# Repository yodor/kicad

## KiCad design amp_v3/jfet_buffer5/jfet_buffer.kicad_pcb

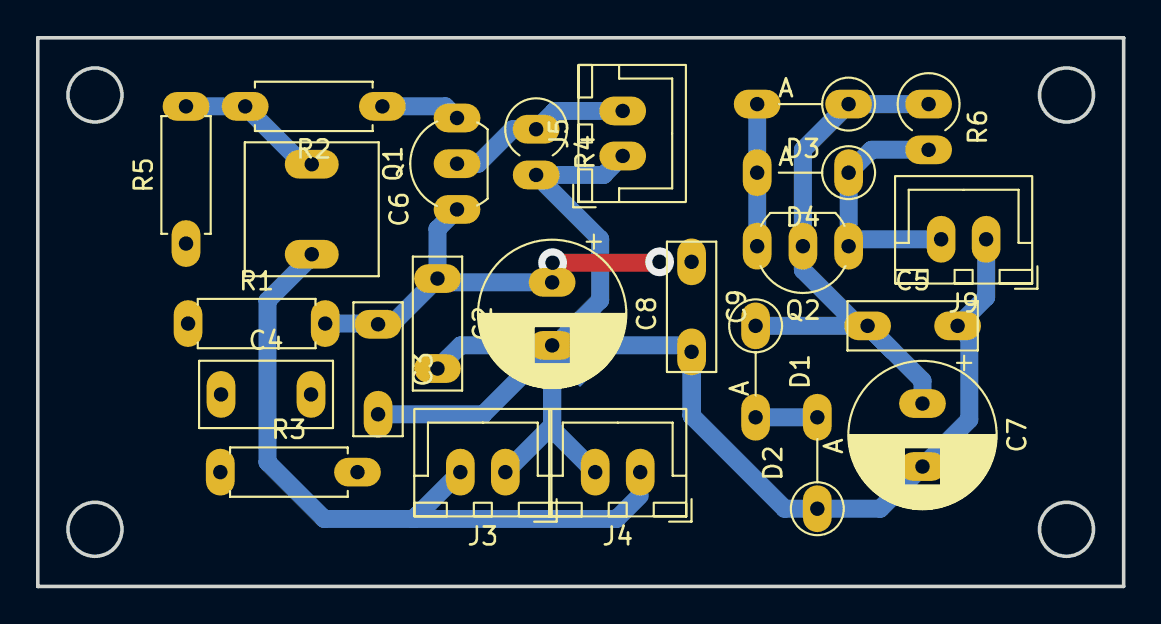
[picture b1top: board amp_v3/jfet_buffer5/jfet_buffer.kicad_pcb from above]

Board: 2 copper layers, 60.3 x 30.5 mm, 25 parts (1 on the bottom side), 10 nets.

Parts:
C2, C3: 100nF; C_Rect_L7.2mm_W2.5mm_P5.00mm_FKS2_FKP2_MKS2_MKP2
C4: 1uF; C_Rect_L7.2mm_W3.5mm_P5.00mm_FKS2_FKP2_MKS2_MKP2
C5, C9: 100nF; C_Rect_L7.0mm_W2.5mm_P5.00mm
C6: 2.2uF; C_Rect_L7.2mm_W7.2mm_P5.00mm_FKS2_FKP2_MKS2_MKP2
C7: 470uF; CP_Radial_D8.0mm_P3.50mm
C8: 470uF (low ESR); CP_Radial_D8.0mm_P3.50mm
D1: 1N4747; D_A-405_P5.08mm_Vertical_AnodeUp
D2: 1n4148; D_A-405_P5.08mm_Vertical_AnodeUp
D3, D4: 1N4007; D_A-405_P5.08mm_Vertical_AnodeUp
J3, J4: AUDIO_IN; JST_XH_B2B-XH-A_1x02_P2.50mm_Vertical
J5: AUDIO_OUT; JST_XH_B2B-XH-A_1x02_P2.50mm_Vertical
J9: PWR_IN; JST_XH_B2B-XH-A_1x02_P2.50mm_Vertical
NT1: NetTie_2; NetTie-2_SMD_Pad1.0o
Q1: 2N5457; TO-92L_Inline_Wide
Q2: BC549C; TO-92_Inline_Wide
R1, R3, R5: 1M; R_Axial_DIN0207_L6.3mm_D2.5mm_P7.62mm_Horizontal
R2: 100; R_Axial_DIN0207_L6.3mm_D2.5mm_P7.62mm_Horizontal
R4: 3.9K; R_Axial_DIN0309_L9.0mm_D3.2mm_P2.54mm_Vertical
R6: 240; R_Axial_DIN0309_L9.0mm_D3.2mm_P2.54mm_Vertical

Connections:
/20V_JFET: C2.1, C3.1, C8.1, C9.1, D3.2 (A), D4.2 (A), Q1.1 (D), Q2.3 (E), R1.2
/22V_REG: D4.1 (K), J9.2, Q2.1 (C), R6.2
/INPUT: C6.2, J3.2, J4.1
/OUT: J5.2, Q1.2 (S), R4.1
/VBIAS: C4.1, R1.1, R3.1, R5.1
/VBIAS_OUT: C6.1, R2.2, R5.2
GND: C2.2, C3.2, C4.2, C5.2, C7.2, C8.2, C9.2, D2.1 (K), J3.1, J4.2, J5.1, J9.1, NT1.2, R3.2, R4.2
unnamed: D1.2 (A), D2.2 (A)
unnamed: C5.1, C7.1, D1.1 (K), D3.1 (K), Q2.2 (B), R6.1
unnamed: Q1.3 (G), R2.1

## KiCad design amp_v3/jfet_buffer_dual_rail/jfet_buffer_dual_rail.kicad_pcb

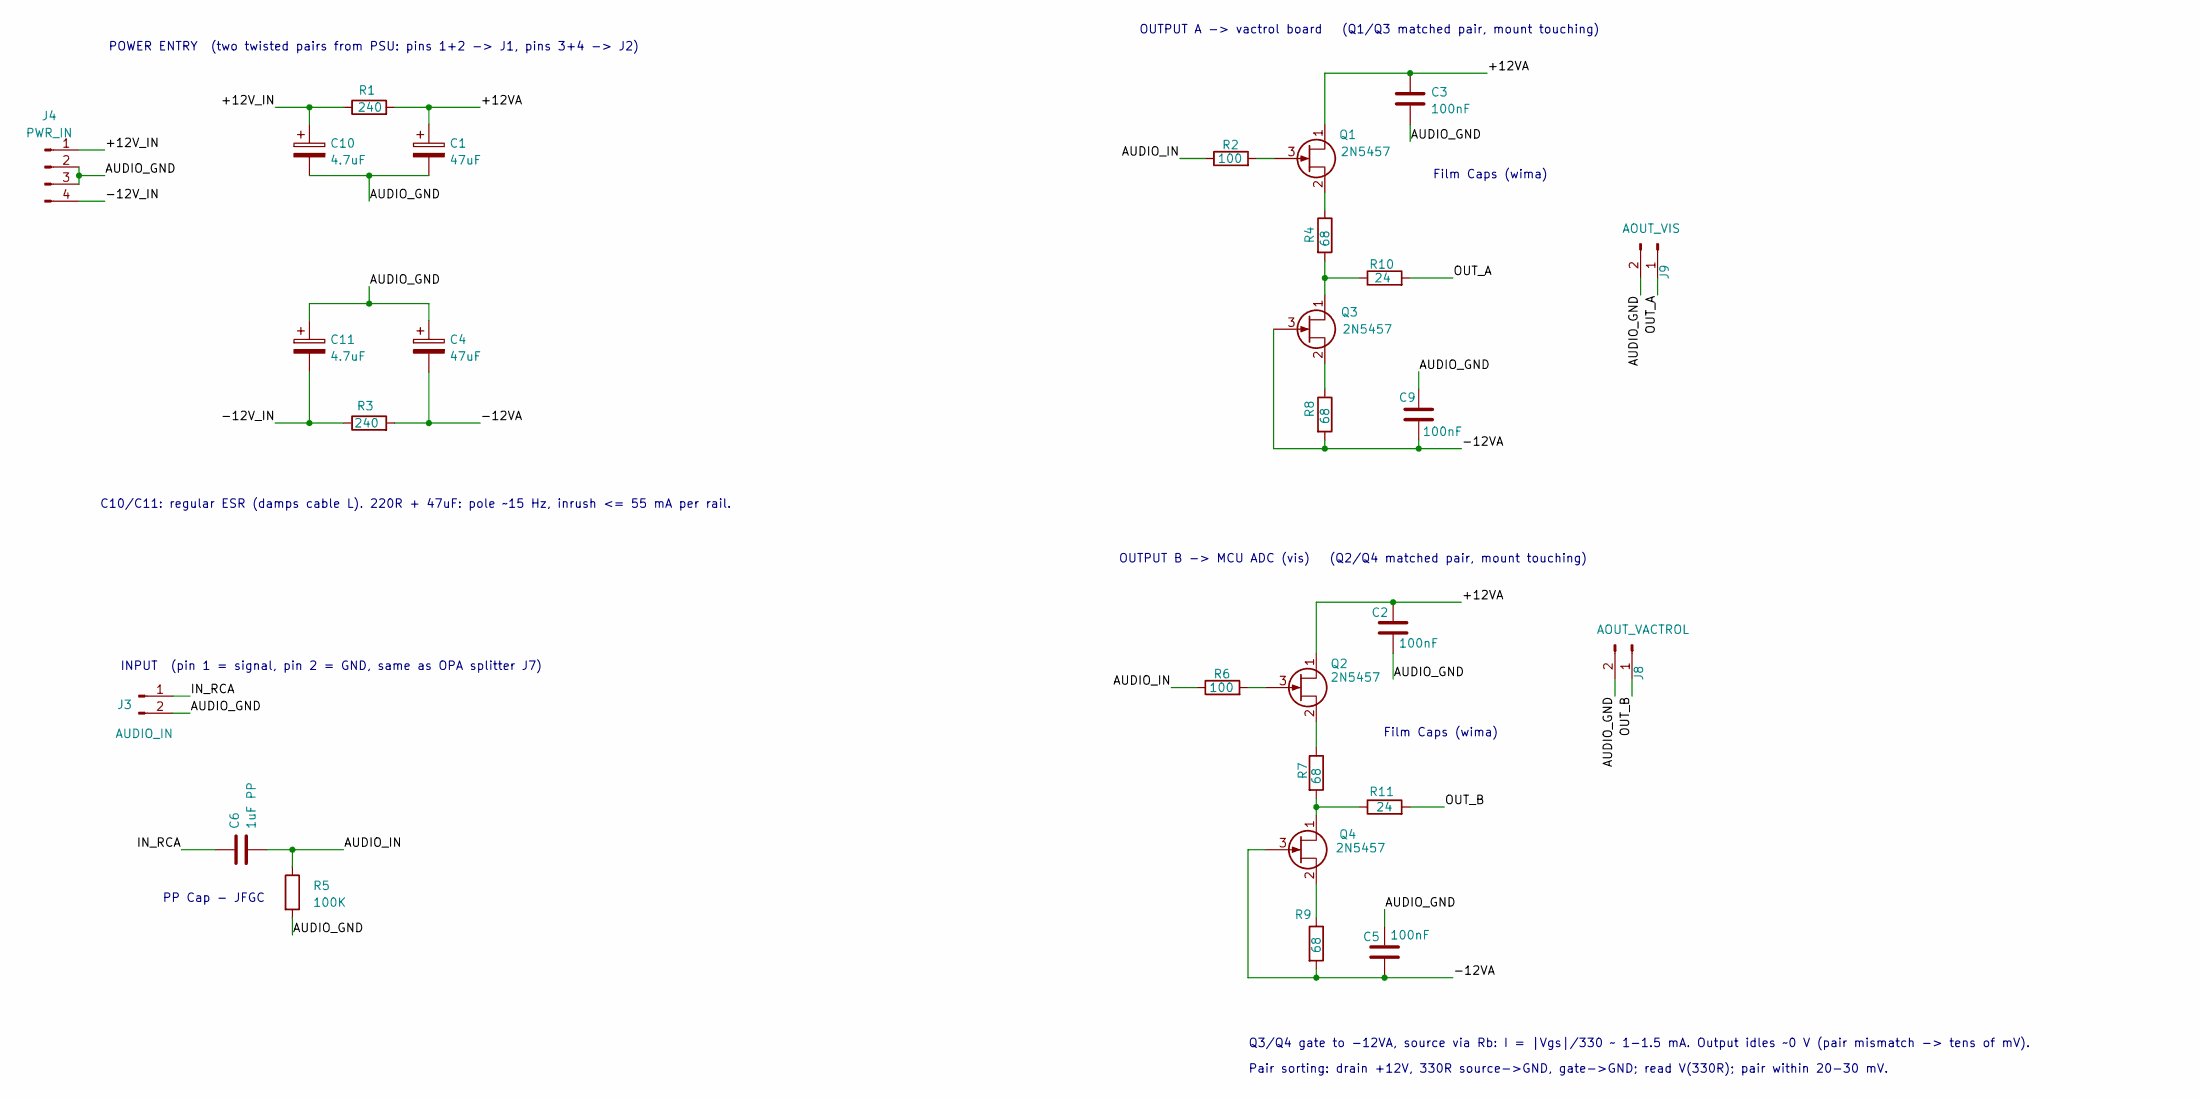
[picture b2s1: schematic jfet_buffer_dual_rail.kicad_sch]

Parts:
C1, C4: 47uF; CP_Radial_D6.3mm_P2.50mm
C2, C3, C5, C9: 100nF; C_Rect_L4.6mm_W3.0mm_P2.50mm_MKS02_FKP02
C6: 1uF PP; JFC
C10, C11: 4.7uF; CP_Radial_D5.0mm_P2.50mm
J3: AUDIO_IN; JST_XH_B2B-XH-A_1x02_P2.50mm_Vertical
J4: PWR_IN; JST_XH_B4B-XH-A_1x04_P2.50mm_Vertical
J8: AOUT_VACTROL; JST_XH_B2B-XH-A_1x02_P2.50mm_Vertical
J9: AOUT_VIS; JST_XH_B2B-XH-A_1x02_P2.50mm_Vertical
Q1, Q2, Q3, Q4: 2N5457; TO-92L_Inline_Wide
R1, R3: 240; R_Axial_DIN0207_L6.3mm_D2.5mm_P7.62mm_Horizontal
R2, R6: 100; R_Axial_DIN0207_L6.3mm_D2.5mm_P7.62mm_Horizontal
R4, R7, R8, R9: 68; R_Axial_DIN0207_L6.3mm_D2.5mm_P7.62mm_Horizontal
R5: 100K; R_Axial_DIN0207_L6.3mm_D2.5mm_P2.54mm_Vertical
R10, R11: 24; R_Axial_DIN0207_L6.3mm_D2.5mm_P7.62mm_Horizontal

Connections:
/+12VA: C1.1, C2.1, C3.1, Q1.1 (D), Q2.1 (D), R1.2
/+12V_IN: C10.1, J4.1, R1.1
/-12VA: C4.2, C5.2, C9.2, Q3.3 (G), Q4.3 (G), R3.2, R8.2, R9.2
/-12V_IN: C11.2, J4.4, R3.1
/AUDIO_GND: C1.2, C2.2, C3.2, C4.1, C5.1, C9.1, C10.2, C11.1, J3.2, J4.2, J4.3, J8.2, J9.2, R5.2
/AUDIO_IN: C6.2, R2.1, R5.1, R6.1
/IN_RCA: C6.1, J3.1
/OUT_A: J9.1, R10.2
/OUT_B: J8.1, R11.2
unnamed: Q1.3 (G), R2.2
unnamed: Q1.2 (S), R4.1
unnamed: Q2.3 (G), R6.2
unnamed: Q2.2 (S), R7.1
unnamed: Q3.1 (D), R4.2, R10.1
unnamed: Q3.2 (S), R8.1
unnamed: Q4.1 (D), R7.2, R11.1
unnamed: Q4.2 (S), R9.1

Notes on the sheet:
POWER ENTRY (two twisted pairs from PSU: pins 1+2 -> J1, pins 3+4 -> J2)
OUTPUT B -> MCU ADC (vis) (Q2/Q4 matched pair, mount touching)
PP Cap - JFGC
Pair sorting: drain +12V, 330R source->GND, gate->GND; read V(330R); pair within 20-30 mV.
C10/C11: regular ESR (damps cable L). 220R + 47uF: pole ~15 Hz, inrush <= 55 mA per rail.
INPUT (pin 1 = signal, pin 2 = GND, same as OPA splitter J7)
OUTPUT A -> vactrol board (Q1/Q3 matched pair, mount touching)
Q3/Q4 gate to -12VA, source via Rb: I = |Vgs|/330 ~ 1-1.5 mA. Output idles ~0 V (pair mismatch -> tens of mV).
Film Caps (wima)

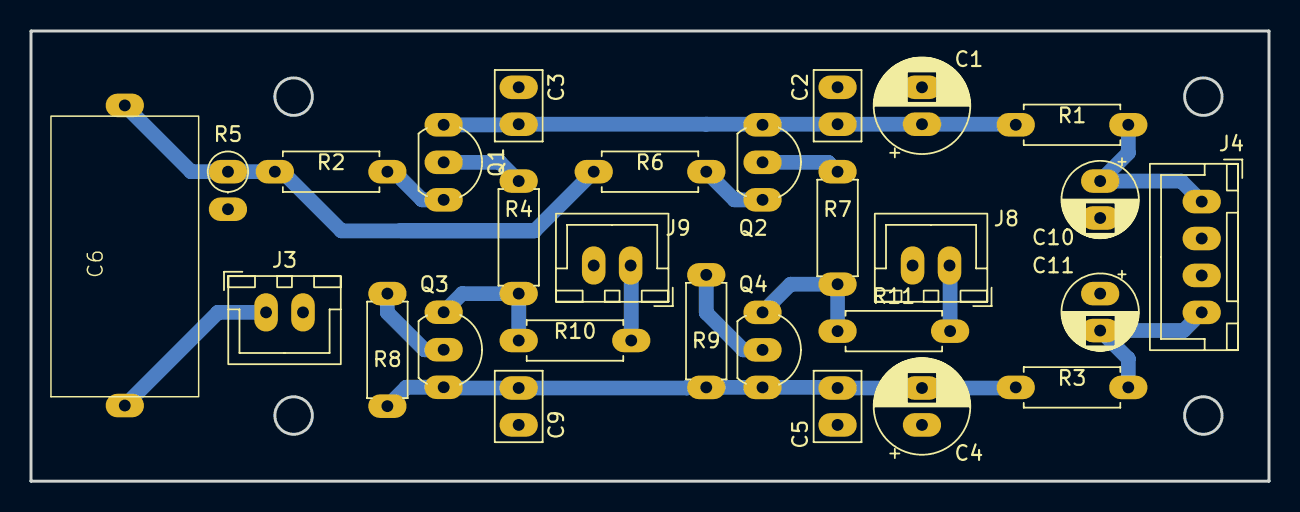
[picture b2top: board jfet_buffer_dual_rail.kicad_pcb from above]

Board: 2 copper layers, 83.8 x 30.5 mm, 28 parts (0 on the bottom side), 17 nets.

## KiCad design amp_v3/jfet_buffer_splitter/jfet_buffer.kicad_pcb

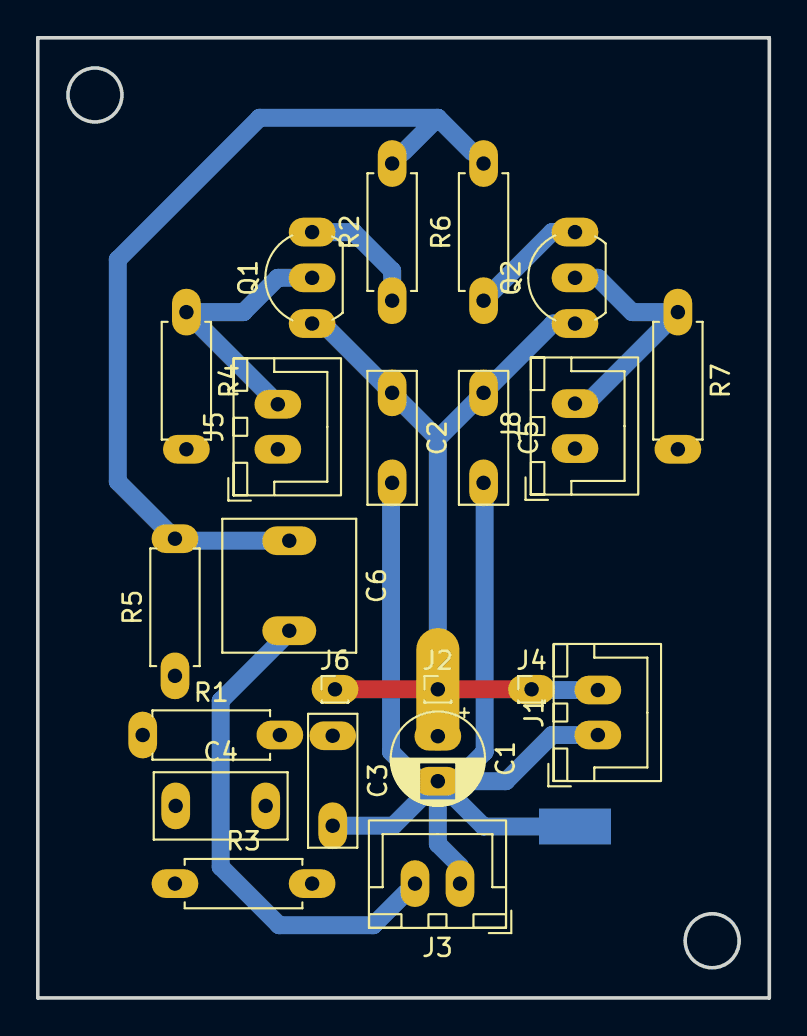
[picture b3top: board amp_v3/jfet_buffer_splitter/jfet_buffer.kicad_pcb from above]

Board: 2 copper layers, 40.6 x 53.3 mm, 23 parts (1 on the bottom side), 9 nets.

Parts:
C1: 100uF; CP_Radial_D5.0mm_P2.50mm
C2, C3, C5: 100nF; C_Rect_L7.2mm_W2.5mm_P5.00mm_FKS2_FKP2_MKS2_MKP2
C4: 1uF; C_Rect_L7.2mm_W3.5mm_P5.00mm_FKS2_FKP2_MKS2_MKP2
C6: 2.2uF; C_Rect_L7.2mm_W7.2mm_P5.00mm_FKS2_FKP2_MKS2_MKP2
J1: PWR; JST_XH_B2B-XH-A_1x02_P2.50mm_Vertical
J2, J4, J6: Conn_01x01_Pin; PinHeader_1x01_P1.00mm_Vertical
J3: INPUT; JST_XH_B2B-XH-A_1x02_P2.50mm_Vertical
J5: OUT1; JST_XH_B2B-XH-A_1x02_P2.50mm_Vertical
J8: OUT2; JST_XH_B2B-XH-A_1x02_P2.50mm_Vertical
NT1: NetTie_2; NetTie-2_SMD_Pad2.0mm
Q1, Q2: 2N5457; TO-92L_Inline_Wide
R1, R3, R5: 1M; R_Axial_DIN0207_L6.3mm_D2.5mm_P7.62mm_Horizontal
R2, R6: 100; R_Axial_DIN0207_L6.3mm_D2.5mm_P7.62mm_Horizontal
R4, R7: 3.9K; R_Axial_DIN0207_L6.3mm_D2.5mm_P7.62mm_Horizontal

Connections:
+20V: C1.1, C2.1, C3.1, C5.1, J1.2, J2.1 (Pin_1_1), J4.1 (Pin_1_1), J6.1 (Pin_1_1), Q1.1 (D), Q2.1 (D), R1.2
/INPUT: C6.2, J3.2
/OUT1: J5.2, Q1.2 (S), R4.1
/OUT2: J8.2, Q2.2 (S), R7.1
/VBIAS: C4.1, R1.1, R3.1, R5.1
/VBIAS_OUT: C6.1, R2.2, R5.2, R6.2
GND: C1.2, C2.2, C3.2, C4.2, C5.2, J1.1, J3.1, J5.1, J8.1, NT1.2, R3.2, R4.2, R7.2
unnamed: Q1.3 (G), R2.1
unnamed: Q2.3 (G), R6.1

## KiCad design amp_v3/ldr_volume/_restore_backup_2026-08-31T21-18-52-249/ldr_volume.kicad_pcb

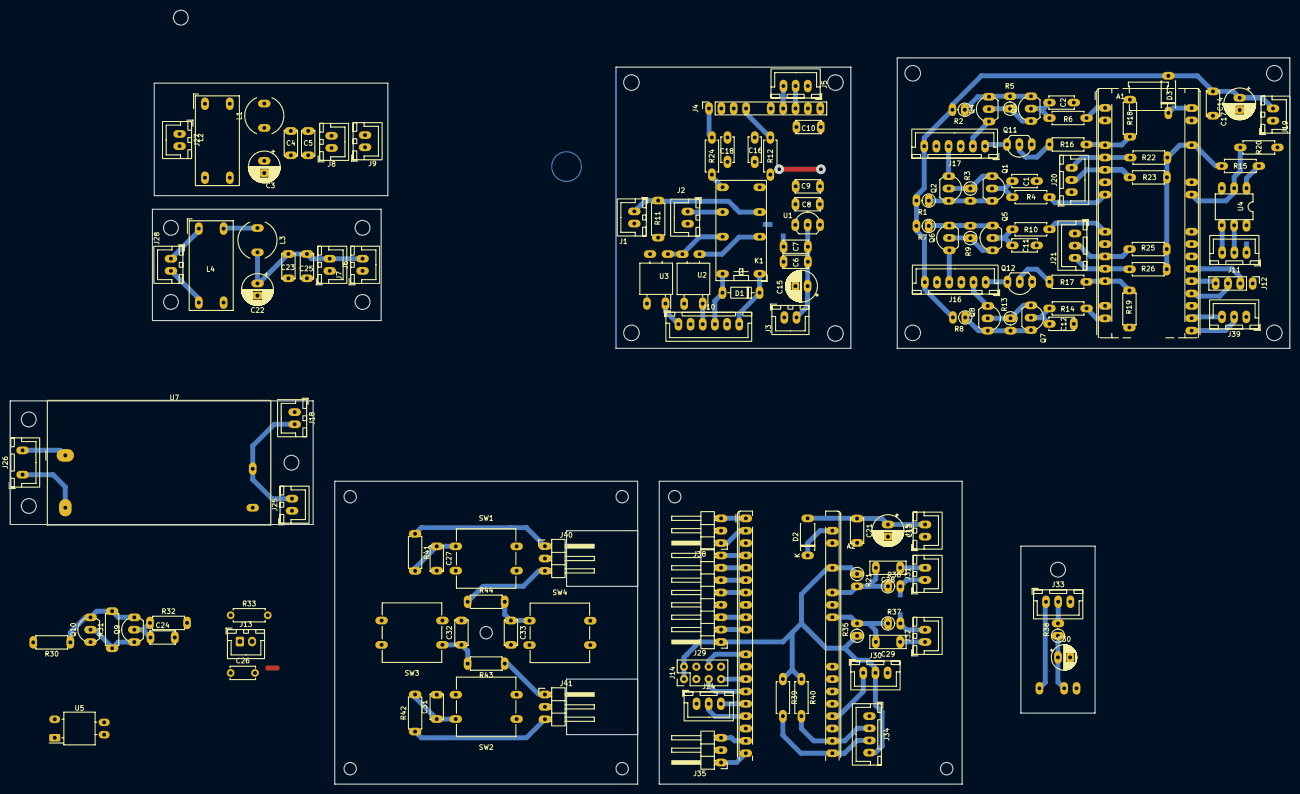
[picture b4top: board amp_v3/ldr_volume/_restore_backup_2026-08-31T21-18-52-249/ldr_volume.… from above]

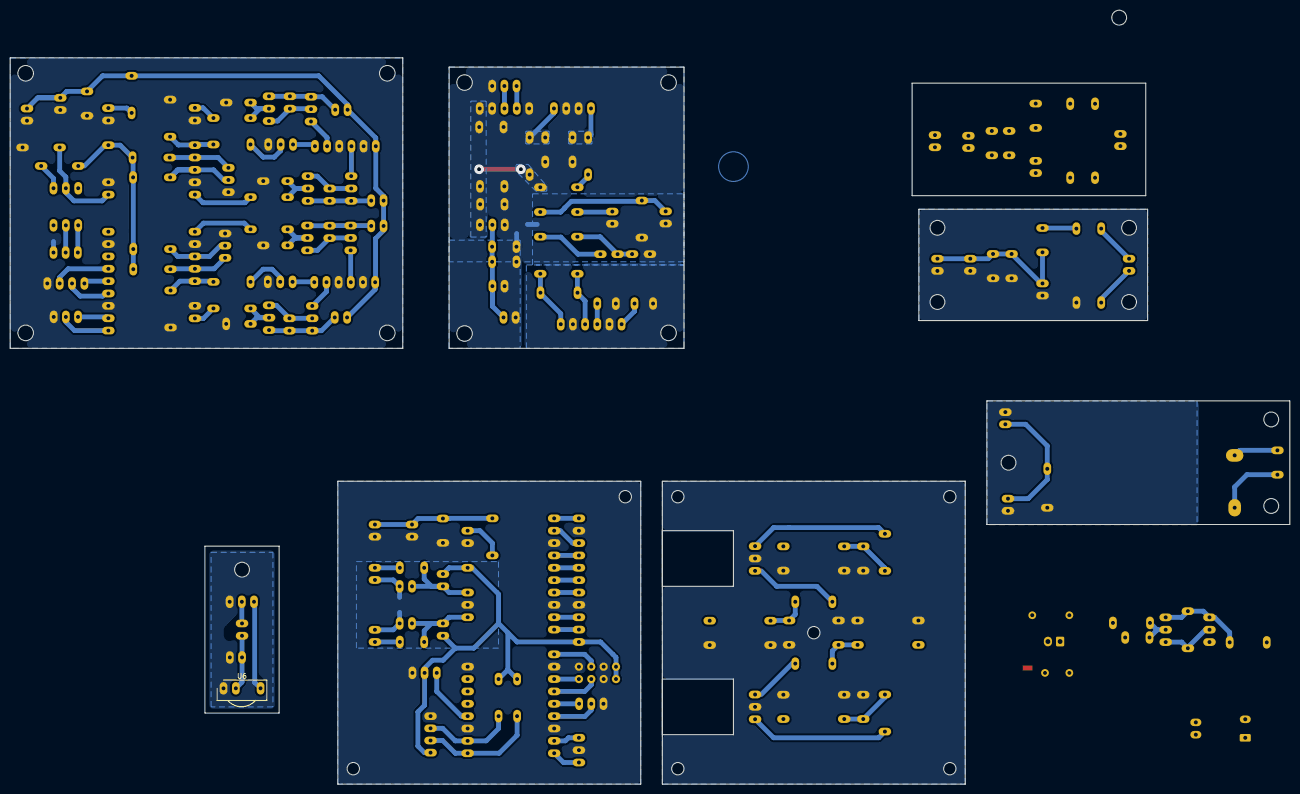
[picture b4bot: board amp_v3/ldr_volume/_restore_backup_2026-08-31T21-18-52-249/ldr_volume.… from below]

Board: 2 copper layers, 262.9 x 159.0 mm, 147 parts (6 on the bottom side), 106 nets.

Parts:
A1, A2: RaspberryPi_Pico_W; RaspberryPi_Pico_Common_THT
C1, C2, C11, C12: 10nF; C_Disc_D5.0mm_W2.5mm_P5.00mm
C3, C22: 100uF (low esr); CP_Radial_D6.3mm_P2.50mm
C4, C23: 10uF; C_Disc_D5.0mm_W2.5mm_P5.00mm
C5, C25: 100nF (X7R); C_Disc_D5.0mm_W2.5mm_P5.00mm
C6, C9: 1uF; C_Disc_D5.0mm_W2.5mm_P5.00mm
C7, C8, C10, C16, C17, C18, C21, C24, C26, C27, C31, C32, C33: 100nF; C_Disc_D5.0mm_W2.5mm_P5.00mm
C13, C14: 100uF low; CP_Radial_D6.3mm_P2.50mm
C15: 100uF; CP_Radial_D6.3mm_P2.50mm
C28, C29: 2.2uF; C_Rect_L7.2mm_W2.5mm_P5.00mm_FKS2_FKP2_MKS2_MKP2
C30: 4.7uF; CP_Radial_D5.0mm_P2.50mm
D1: 1n4007; D_DO-35_SOD27_P7.62mm_Horizontal
D2, D3: 1n5819; D_DO-41_SOD81_P7.62mm_Horizontal
J1: A_IN; JST_XH_B2B-XH-A_1x02_P2.50mm_Vertical
J2: A_OUT; JST_XH_B2B-XH-A_1x02_P2.50mm_Vertical
J3: 5v_in; JST_XH_B2B-XH-A_1x02_P2.50mm_Vertical
J4: ADS1115; PinSocket_1x10_P2.54mm_Vertical
J5, J21: I2C_R; JST_XH_B3B-XH-A_1x03_P2.50mm_Vertical
J6: PWR1; JST_XH_B2B-XH-A_1x02_P2.50mm_Vertical
J7: PWR2; JST_XH_B2B-XH-A_1x02_P2.50mm_Vertical
J8, J18: PWR3; JST_XH_B2B-XH-A_1x02_P2.50mm_Vertical
J9, J25: PWR4; JST_XH_B2B-XH-A_1x02_P2.50mm_Vertical
J10, J16, J17: CTRL; JST_XH_B6B-XH-A_1x06_P2.50mm_Vertical
J11: MUTE; JST_XH_B3B-XH-A_1x03_P2.50mm_Vertical
J12: EXT; PinHeader_1x04_P2.54mm_Vertical
J13: NTC; JST_XH_B2B-XH-A_1x02_P2.50mm_Vertical
J14: Conn_02x04_Counter_Clockwise; PinHeader_2x04_P2.54mm_Vertical
J15, J19: PWR_IN; JST_XH_B2B-XH-A_1x02_P2.50mm_Vertical
J20: I2C_L; JST_XH_B3B-XH-A_1x03_P2.50mm_Vertical
J24, J39: UART; JST_XH_B3B-XH-A_1x03_P2.50mm_Vertical
J26: Conn_01x03_Pin; JST_XH_B3B-XH-A_1x03_P2.50mm_Vertical
J27, J28: 5V_IN; JST_XH_B2B-XH-A_1x02_P2.50mm_Vertical
J29: TFT; PinHeader_1x08_P2.54mm_Horizontal
J30, J33: IR; JST_XH_B3B-XH-A_1x03_P2.50mm_Vertical
J31: S_AIN_L; JST_XH_B2B-XH-A_1x02_P2.50mm_Vertical
J32: S_AIN_R; JST_XH_B2B-XH-A_1x02_P2.50mm_Vertical
J34: SDA; JST_XH_B4B-XH-A_1x04_P2.50mm_Vertical
J35: BTN_VOL; PinHeader_1x03_P2.54mm_Horizontal
J38: BTN_MENU; PinHeader_1x03_P2.54mm_Horizontal
J40: BTN_EXT1; PinHeader_1x03_P2.54mm_Horizontal
J41: BTN_EXT2; PinHeader_1x03_P2.54mm_Horizontal
K1: G5V-2; Relay_DPDT_Omron_G5V-2
L1, L3: 10uH; L_Radial_D7.8mm_P5.00mm_Fastron_07HCP
L2: RN202-0.3-02-12M; Choke_Schaffner_RN202-04-8.8x18.2mm
L4: RN-202-1/02; Choke_Schaffner_RN202-04-8.8x18.2mm
NT1, NT4: GNDD_TO_GNDA; NetTie-2_SMD_Pad1.0o
NT2: AUDIOGND_TO_GNDA; NetTie-2_SMD_Pad1.0o
NT3: mute_cable; NetTie-2_SMD_Pad1.0o
NT7, NT8: NetTie_2; NetTie-2_SMD_Pad1.0o
Q1, Q3, Q5, Q7, Q9: BC547; TO-92_Inline_Wide
Q2, Q4, Q6, Q8, Q10: BC557; TO-92_Inline_Wide
Q11, Q12: 2N7000; TO-92_Inline_Wide
R1, R2, R7, R8: 120; R_Axial_DIN0207_L6.3mm_D2.5mm_P2.54mm_Vertical
R3, R5, R9, R13: 100K; R_Axial_DIN0207_L6.3mm_D2.5mm_P2.54mm_Vertical
R4, R6, R10, R14, R18, R19, R20, R32, R33: 10K; R_Axial_DIN0207_L6.3mm_D2.5mm_P7.62mm_Horizontal
R11, R31: 100K; R_Axial_DIN0207_L6.3mm_D2.5mm_P7.62mm_Horizontal
R12, R24: 1K; R_Axial_DIN0207_L6.3mm_D2.5mm_P7.62mm_Horizontal
R15: 300; R_Axial_DIN0207_L6.3mm_D2.5mm_P7.62mm_Horizontal
R16, R17: 100R; R_Axial_DIN0207_L6.3mm_D2.5mm_P7.62mm_Horizontal
R21, R35, R36, R37, R38: 10K; R_Axial_DIN0207_L6.3mm_D2.5mm_P2.54mm_Vertical
R22, R23, R25, R26, R39, R40: 4.7K; R_Axial_DIN0207_L6.3mm_D2.5mm_P7.62mm_Horizontal
R30: 110; R_Axial_DIN0207_L6.3mm_D2.5mm_P7.62mm_Horizontal
R41, R42, R43, R44: 1k; R_Axial_DIN0207_L6.3mm_D2.5mm_P7.62mm_Horizontal
SW1, SW2, SW3, SW4: SW_Push; SW_SPST_Omron_B3F-50xx
U1: MCP1700x-330xxTO; TO-92_Inline_Wide
U2: NSL-32-SR3-Rseries; Luna_NSL-32
U3: NSL-32-SR3-Rshunt; Luna_NSL-32
U4: 4N25; DIP-6_W7.62mm
U5: NSL-32-SR3; Luna_NSL-32
U6: TSOP312xx; Vishay_CAST-3Pin
U7: IRM-10-5; Converter_ACDC_MeanWell_IRM-10-xx_THT

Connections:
/board#1/5V_IRM: J18.2, J25.2, J27.1, J28.1, L2.1, L4.1, U7.4 (+Vo)
/board#1/5V_analog: C3.1, C4.1, C5.1, J8.2, J9.2, L1.2
/board#1/5V_board1: C22.1, C23.1, C25.1, J6.2, J7.2, L3.2
/board#1/GND_IRM: J18.1, J25.1, J27.2, J28.2, L2.3, L4.3, U7.3 (-Vo)
/board#2/5v_ads: C6.1, C7.1, C15.1, J3.2, U1.2 (VI)
/board#2/5v_local: D1.1 (K), J10.6, K1.1
/board#2/A0: C16.1, J4.4, R12.1
/board#2/A3: C18.1, J4.1, R24.1
/board#2/ADS_VDD: C8.1, C9.1, C10.1, J4.10, K1.8, R12.2, U1.3 (VO)
/board#2/AUDIO_IN: J1.1, K1.6, R11.2
/board#2/AUDIO_OUT: J2.1, K1.11
/board#2/COIL_NEG: D1.2 (A), J10.4, K1.16
/board#2/MIDDLE_JUNCTION: K1.9, R24.2
/board#2/SCL: J4.8, J5.2
/board#2/SDA: J4.7, J5.3
/board#2/SERIAL_POS: J10.3, U2.1 (A)
/board#2/SHUNT_POS: J10.1, U3.1 (A)
/board#3/3.3V_PICO: A1.36 (3V3), R15.2, R22.1, R23.1, R25.1, R26.1
/board#3/5V_board1: C14.1, C17.1, D3.2 (A), J16.6, J17.6, J19.2, R1.2, R2.2, R7.2, R8.2
/board#3/AMP_GND_PIN: J11.3, U4.4
/board#3/AMP_MUTE_PIN: J11.2, U4.5
/board#3/CABLE_SHD: J11.1, NT3.1
/board#3/COIL_CTRL_L: A1.5 (GPIO3), R16.1, R18.1
/board#3/COIL_CTRL_R: A1.16 (GPIO12), R17.1, R19.1
/board#3/COIL_L: J17.1, Q11.3 (D)
/board#3/COIL_R: J16.1, Q12.3 (D)
/board#3/EXT1: A1.25 (GPIO19), J12.4
/board#3/EXT2: A1.24 (GPIO18), J12.3
/board#3/EXT3: A1.26 (GPIO20), J12.2
/board#3/MUTE_CTRL: A1.32 (GPIO27_ADC1), R20.1, U4.2
/board#3/PWM_SER_L: A1.2 (GPIO1), R6.2
/board#3/PWM_SER_R: A1.19 (GPIO14), R14.2
/board#3/PWM_SHUNT_L: A1.9 (GPIO6), R4.2
/board#3/PWM_SHUNT_R: A1.12 (GPIO9), R10.2
/board#3/SCL_L: A1.7 (GPIO5), J20.2, R23.2
/board#3/SCL_R: A1.15 (GPIO11), J21.3, R26.2
/board#3/SDA_L: A1.6 (GPIO4), J20.3, R22.2
/board#3/SDA_R: A1.14 (GPIO10), J21.2, R25.2
/board#3/SERIAL_L: J17.2, Q4.1 (C)
/board#3/SERIAL_R: J16.2, Q8.1 (C)
/board#3/SHUNT_L: J17.4, Q2.1 (C)
/board#3/SHUNT_R: J16.4, Q6.1 (C)
/board#3/UART_RX: A1.21 (GPIO16), J39.2
/board#3/UART_TX: A1.22 (GPIO17), J39.3
/board#5/3.3V_PICO: A2.36 (3V3), J14.1, J14.2, J29.1, J30.2, J33.2, J34.4, R21.1, R35.1, R38.2, R39.1, R40.1
/board#5/5V_board1: C13.1, C21.1, D2.2 (A), J15.2
/board#5/ADC_L: A2.34 (GPIO28_ADC2), C28.2, R21.2, R36.1
/board#5/ADC_R: A2.32 (GPIO27_ADC1), C29.2, R35.2, R37.1
/board#5/AGND_L: J31.1, NT8.1, R36.2
/board#5/AGND_PICO: A2.33 (AGND), NT7.2, NT8.2
/board#5/AGND_R: J32.2, NT7.1, R37.2
/board#5/AUDIO_L: C28.1, J31.2
/board#5/AUDIO_R: C29.1, J32.1
/board#5/BTN_DN: A2.19 (GPIO14), J35.3, J41.3, R42.1
/board#5/BTN_LT: A2.20 (GPIO15), J35.1, J41.1, R43.1
/board#5/BTN_RT: A2.2 (GPIO1), J38.1, J40.3, R44.1
/board#5/BTN_UP: A2.1 (GPIO0), J38.3, J40.1, R41.1
/board#5/EXT_1: A2.14 (GPIO10), J14.7
/board#5/EXT_2: A2.15 (GPIO11), J14.5
/board#5/IR: A2.24 (GPIO18), J30.1, J33.1, U6.3 (OUT)
/board#5/PWR_CTRL: A2.12 (GPIO9), J14.6
/board#5/SCL: A2.22 (GPIO17), J34.2, R40.2
/board#5/SDA: A2.21 (GPIO16), J34.3, R39.2
/board#5/TFT_BLK: A2.6 (GPIO4), J29.6
/board#5/TFT_CS: A2.7 (GPIO5), J29.5
/board#5/TFT_DC: A2.9 (GPIO6), J29.3
/board#5/TFT_RST: A2.10 (GPIO7), J29.2
/board#5/TFT_SCL: A2.4 (GPIO2), J29.8
/board#5/TFT_SDA: A2.5 (GPIO3), J29.7
/board#5/UART_RX: A2.17 (GPIO13), J24.2
/board#5/UART_TX: A2.16 (GPIO12), J24.3
/testboard/TEMP_IN: C26.1, J13.1, R33.1
AUDIO_GND: J1.2, J2.2, NT2.1, R11.1, U3.3 (R)
GNDA: C8.2, C9.2, C10.2, C16.2, C18.2, C26.2, J4.2, J4.3, J4.6, J4.9, J5.1, NT1.2, NT2.2, NT4.2, R33.2, U1.1 (GND)
GNDD: A1.3 (GND), A1.8 (GND), A1.13 (GND), A1.18 (GND), A1.23 (GND), A1.28 (GND), A1.33 (AGND), A1.38 (GND), A2.3 (GND), A2.8 (GND), A2.13 (GND), A2.18 (GND), A2.23 (GND), A2.28 (GND), A2.38 (GND), C1.2, C2.2, C3.2, C4.2, C5.2, C6.2, C7.2, C11.2, C12.2, C13.2, C14.2, C15.2, C17.2, C21.2, C22.2, C23.2, C24.2, C25.2, C27.2, C30.2, C31.2, C32.2, C33.2, J3.1, J6.1, J7.1, J8.1, J9.1, J10.2, J10.5, J12.1, J14.3, J14.4, J14.8, J15.1, J16.3, J16.5, J17.3, J17.5, J19.1, J20.1, J21.1, J24.1, J29.4, J30.3, J33.3, J34.1, J35.2, J38.2, J39.1, J40.2, J41.2, L2.4, L4.4, NT1.1, NT3.2, NT4.1, Q11.1 (S), Q12.1 (S), R18.2, R19.2, R20.2, SW1.2, SW2.2, SW3.2, SW4.2, U2.2 (K), U3.2 (K), U6.1 (GND)
unnamed: A1.39 (VSYS), D3.1 (K)
unnamed: A2.39 (VSYS), D2.1 (K)
unnamed: C27.1, R41.2, SW1.1
unnamed: C31.1, R42.2, SW2.1
unnamed: C32.1, R43.2, SW3.1
unnamed: C33.1, R44.2, SW4.1
unnamed: J26.1, U7.2 (AC/L)
unnamed: J26.3, U7.1 (AC/N)
unnamed: K1.4, U2.4 (R)
unnamed: K1.13, U2.3 (R), U3.4 (R)
unnamed: L1.1, L2.2
unnamed: L3.1, L4.2
unnamed: C1.1, Q1.2 (B), R4.1
unnamed: Q1.1 (C), Q2.2 (B), R3.1
unnamed: Q1.3 (E), Q2.3 (E), R1.1, R3.2
unnamed: C2.1, Q3.2 (B), R6.1
unnamed: Q3.1 (C), Q4.2 (B), R5.1
unnamed: Q3.3 (E), Q4.3 (E), R2.1, R5.2
unnamed: C11.1, Q5.2 (B), R10.1
unnamed: Q5.1 (C), Q6.2 (B), R9.1
unnamed: Q5.3 (E), Q6.3 (E), R7.1, R9.2
unnamed: C12.1, Q7.2 (B), R14.1
unnamed: Q7.1 (C), Q8.2 (B), R13.1
unnamed: Q7.3 (E), Q8.3 (E), R8.1, R13.2
unnamed: C24.1, Q9.2 (B), R32.1
unnamed: Q9.1 (C), Q10.2 (B), R31.1
unnamed: Q9.3 (E), Q10.3 (E), R30.1, R31.2
unnamed: Q11.2 (G), R16.2
unnamed: Q12.2 (G), R17.2
unnamed: R15.1, U4.1
unnamed: C30.1, R38.1, U6.2 (Vs)

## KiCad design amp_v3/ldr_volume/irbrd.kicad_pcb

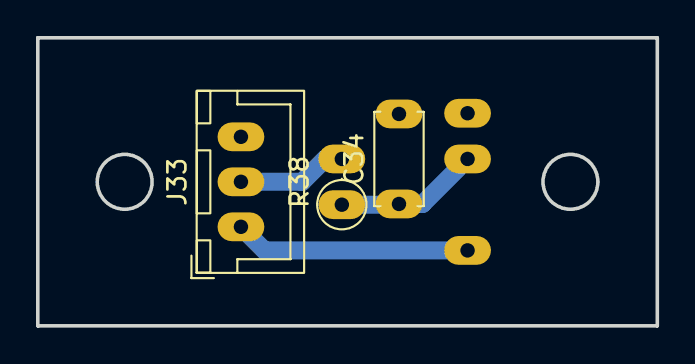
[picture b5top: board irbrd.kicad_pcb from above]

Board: 2 copper layers, 34.4 x 16.0 mm, 4 parts (1 on the bottom side), 4 nets.

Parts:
C34: 100nF; C_Disc_D5.0mm_W2.5mm_P5.00mm
J33: IR_SENSOR; JST_XH_B3B-XH-A_1x03_P2.50mm_Vertical
R38: 100; R_Axial_DIN0207_L6.3mm_D2.5mm_P2.54mm_Vertical
U6: TSOP312xx; Vishay_CAST-3Pin

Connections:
/board#5/3.3V_PICO: J33.2, R38.2
/board#5/IR: J33.1, U6.3 (OUT)
GNDD: C34.2, J33.3, U6.1 (GND)
unnamed: C34.1, R38.1, U6.2 (Vs)
